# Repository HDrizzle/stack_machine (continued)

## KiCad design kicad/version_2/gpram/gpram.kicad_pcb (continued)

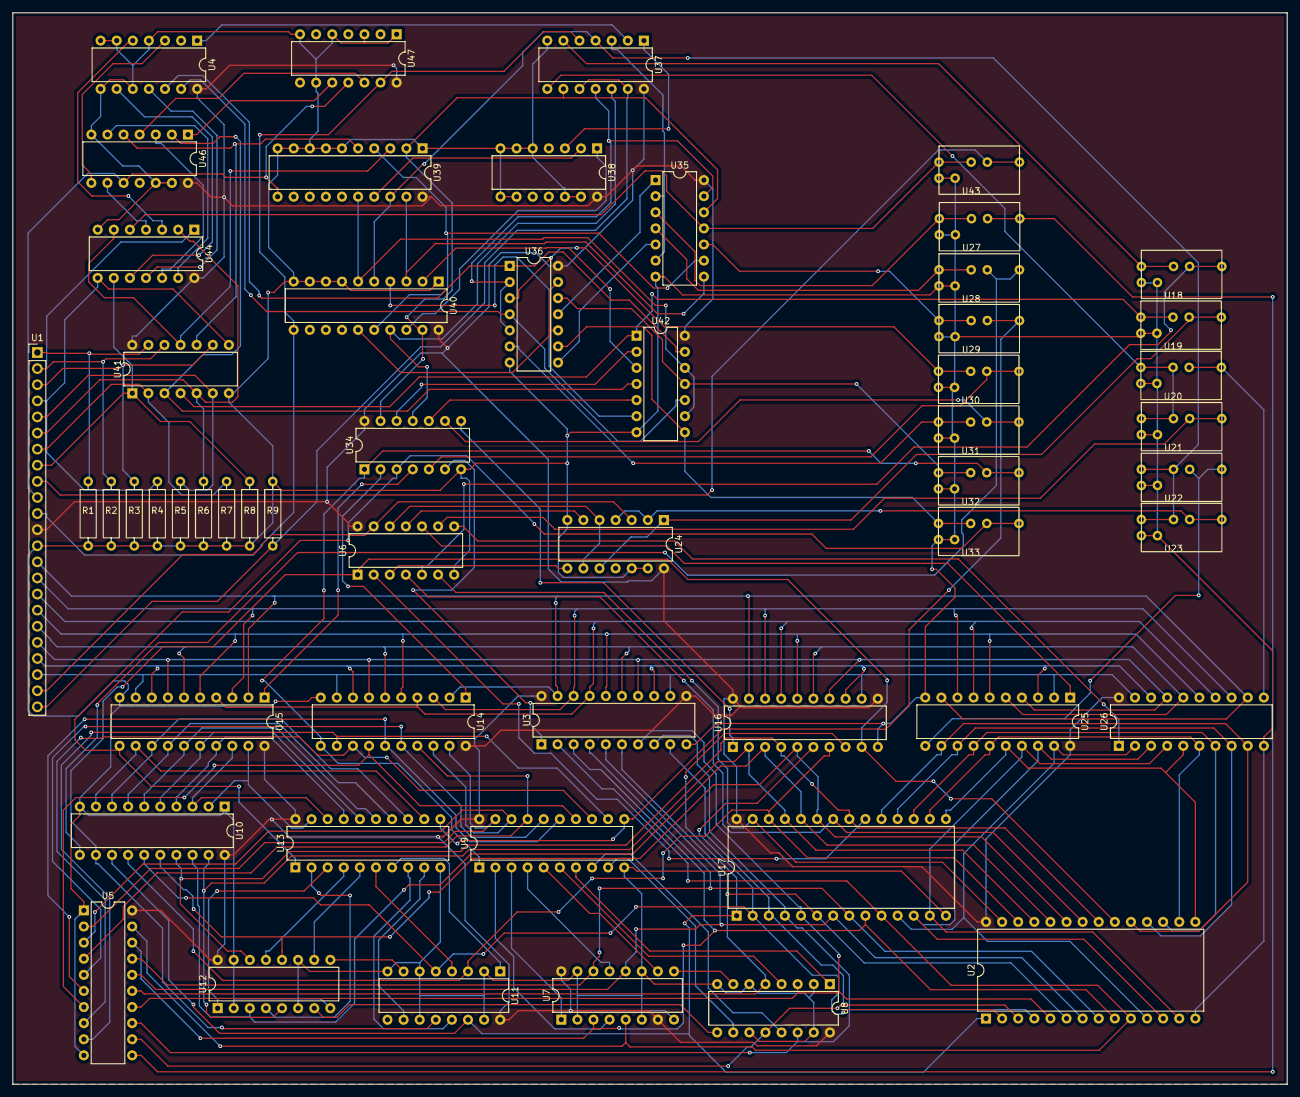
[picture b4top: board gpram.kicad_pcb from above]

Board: 2 copper layers, 201.0 x 169.0 mm, 55 parts (0 on the bottom side), 151 nets.

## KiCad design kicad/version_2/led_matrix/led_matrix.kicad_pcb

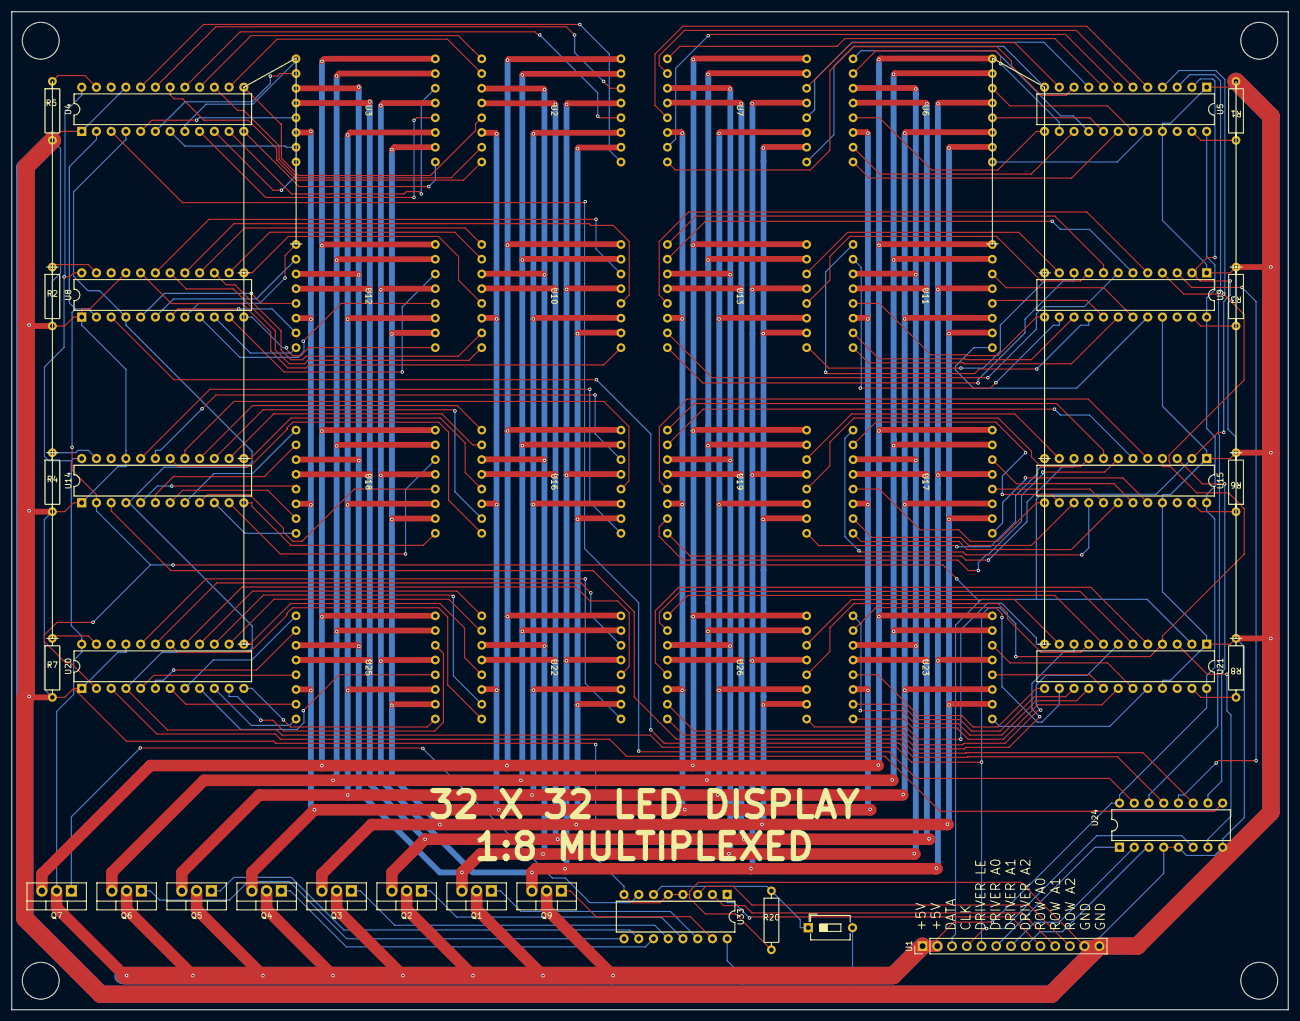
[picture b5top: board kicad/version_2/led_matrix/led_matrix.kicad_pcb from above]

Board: 2 copper layers, 220.0 x 172.0 mm, 45 parts (0 on the bottom side), 172 nets.

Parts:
Q1, Q2, Q3, Q4, Q5, Q6, Q7, Q9: IRF540N; TO-220-3_Vertical
R1, R2, R3, R4, R5, R6, R7, R8, R20: R; 0.4_pitch_resistor
SW1: SW_DIP_x01; SW_DIP_SPSTx01_Slide_6.7x4.1mm_W7.62mm_P2.54mm_LowProfile
U1: PinHeader_1x13_P2.54mm_Vertical
U2, U3, U6, U7, U10, U11, U12, U13, U16, U17, U18, U19, U22, U23, U25, U26: 8_x_8_led_matrix_KWM-30881CVB
U4, U5, U8, U9, U14, U15, U20, U21: DIP-24_W7.62mm
U24, U33: DIP-16_W7.62mm

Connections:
unnamed: Q1.2 (D), Q2.2 (D), Q3.2 (D), Q4.2 (D), Q5.2 (D), Q6.2 (D), Q7.2 (D), Q9.2 (D), SW1.2, U1.1 (V+), U1.2 (V+), U4.24 (V+), U5.24 (V+), U8.24 (V+), U9.24 (V+), U14.24 (V+), U15.24 (V+), U20.24 (V+), U21.24 (V+), U24.16 (V+), U33.16 (V+)
unnamed: Q1.1 (G), U33.14 (Y1)
unnamed: Q1.3 (S), U2.3 (C1), U3.3 (C1), U6.3 (C1), U7.3 (C1), U10.3 (C1), U11.3 (C1), U12.3 (C1), U13.3 (C1), U16.3 (C1), U17.3 (C1), U18.3 (C1), U19.3 (C1), U22.3 (C1), U23.3 (C1), U25.3 (C1), U26.3 (C1)
unnamed: Q2.1 (G), U33.13 (Y2)
unnamed: Q2.3 (S), U2.4 (C2), U3.4 (C2), U6.4 (C2), U7.4 (C2), U10.4 (C2), U11.4 (C2), U12.4 (C2), U13.4 (C2), U16.4 (C2), U17.4 (C2), U18.4 (C2), U19.4 (C2), U22.4 (C2), U23.4 (C2), U25.4 (C2), U26.4 (C2)
unnamed: Q3.1 (G), U33.12 (Y3)
unnamed: Q3.3 (S), U2.10 (C3), U3.10 (C3), U6.10 (C3), U7.10 (C3), U10.10 (C3), U11.10 (C3), U12.10 (C3), U13.10 (C3), U16.10 (C3), U17.10 (C3), U18.10 (C3), U19.10 (C3), U22.10 (C3), U23.10 (C3), U25.10 (C3), U26.10 (C3)
unnamed: Q4.1 (G), U33.11 (Y4)
unnamed: Q4.3 (S), U2.6 (C4), U3.6 (C4), U6.6 (C4), U7.6 (C4), U10.6 (C4), U11.6 (C4), U12.6 (C4), U13.6 (C4), U16.6 (C4), U17.6 (C4), U18.6 (C4), U19.6 (C4), U22.6 (C4), U23.6 (C4), U25.6 (C4), U26.6 (C4)
unnamed: Q5.1 (G), U33.10 (Y5)
unnamed: Q5.3 (S), U2.11 (C5), U3.11 (C5), U6.11 (C5), U7.11 (C5), U10.11 (C5), U11.11 (C5), U12.11 (C5), U13.11 (C5), U16.11 (C5), U17.11 (C5), U18.11 (C5), U19.11 (C5), U22.11 (C5), U23.11 (C5), U25.11 (C5), U26.11 (C5)
unnamed: Q6.1 (G), U33.9 (Y6)
unnamed: Q6.3 (S), U2.15 (C6), U3.15 (C6), U6.15 (C6), U7.15 (C6), U10.15 (C6), U11.15 (C6), U12.15 (C6), U13.15 (C6), U16.15 (C6), U17.15 (C6), U18.15 (C6), U19.15 (C6), U22.15 (C6), U23.15 (C6), U25.15 (C6), U26.15 (C6)
unnamed: Q7.1 (G), U33.7 (Y7)
unnamed: Q7.3 (S), U2.16 (C7), U3.16 (C7), U6.16 (C7), U7.16 (C7), U10.16 (C7), U11.16 (C7), U12.16 (C7), U13.16 (C7), U16.16 (C7), U17.16 (C7), U18.16 (C7), U19.16 (C7), U22.16 (C7), U23.16 (C7), U25.16 (C7), U26.16 (C7)
unnamed: Q9.1 (G), U33.15 (Y0)
unnamed: Q9.3 (S), U2.13 (C0), U3.13 (C0), U6.13 (C0), U7.13 (C0), U10.13 (C0), U11.13 (C0), U12.13 (C0), U13.13 (C0), U16.13 (C0), U17.13 (C0), U18.13 (C0), U19.13 (C0), U22.13 (C0), U23.13 (C0), U25.13 (C0), U26.13 (C0)
unnamed: U1.4 (CLK), U24.6 (E1)
unnamed: U1.3 (Data), U4.2 (D_in), U5.2 (D_in), U8.2 (D_in), U9.2 (D_in), U14.2 (D_in), U15.2 (D_in), U20.2 (D_in), U21.2 (D_in)
unnamed: U1.6 (Driver_A0), U24.1 (A0)
unnamed: U1.7 (Driver_A1), U24.2 (A1)
unnamed: U1.8 (Driver_A2), U24.3 (A2)
unnamed: U1.5 (Driver_LE), U4.4 (LE), U5.4 (LE), U8.4 (LE), U9.4 (LE), U14.4 (LE), U15.4 (LE), U20.4 (LE), U21.4 (LE)
unnamed: U1.9 (Row_A0), U33.1 (A0)
unnamed: U1.10 (Row_A1), U33.2 (A1)
unnamed: U1.11 (Row_A2), U33.3 (A2)
unnamed: U2.9 (R0), U4.20 (O15)
unnamed: U2.14 (R1), U4.19 (O14)
unnamed: U2.8 (R2), U4.18 (O13)
unnamed: U2.12 (R3), U4.17 (O12)
unnamed: U2.1 (R4), U4.16 (O11)
unnamed: U2.7 (R5), U4.15 (O10)
unnamed: U2.2 (R6), U4.14 (O9)
unnamed: U2.5 (R7), U4.13 (O8)
unnamed: U3.9 (R0), U4.12 (O7)
unnamed: U3.14 (R1), U4.11 (O6)
unnamed: U3.8 (R2), U4.10 (O5)
unnamed: U3.12 (R3), U4.9 (O4)
unnamed: U3.1 (R4), U4.8 (O3)
unnamed: U3.7 (R5), U4.7 (O2)
unnamed: U3.2 (R6), U4.6 (O1)
unnamed: U3.5 (R7), U4.5 (O0)
unnamed: R5.1, U4.23 (SET)
unnamed: U5.5 (O0), U7.5 (R7)
unnamed: U5.6 (O1), U7.2 (R6)
unnamed: U5.7 (O2), U7.7 (R5)
unnamed: U5.8 (O3), U7.1 (R4)
unnamed: U5.9 (O4), U7.12 (R3)
unnamed: U5.10 (O5), U7.8 (R2)
unnamed: U5.11 (O6), U7.14 (R1)
unnamed: U5.12 (O7), U7.9 (R0)
unnamed: U5.13 (O8), U6.5 (R7)
unnamed: U5.14 (O9), U6.2 (R6)
unnamed: U5.15 (O10), U6.7 (R5)
unnamed: U5.16 (O11), U6.1 (R4)
unnamed: U5.17 (O12), U6.12 (R3)
unnamed: U5.18 (O13), U6.8 (R2)
unnamed: U5.19 (O14), U6.14 (R1)
unnamed: U5.20 (O15), U6.9 (R0)
unnamed: R1.1, U5.23 (SET)
unnamed: R2.1, U8.23 (SET)
unnamed: R3.1, U9.23 (SET)
unnamed: U8.20 (O15), U10.9 (R0)
unnamed: U8.19 (O14), U10.14 (R1)
unnamed: U8.18 (O13), U10.8 (R2)
unnamed: U8.17 (O12), U10.12 (R3)
unnamed: U8.16 (O11), U10.1 (R4)
unnamed: U8.15 (O10), U10.7 (R5)
unnamed: U8.14 (O9), U10.2 (R6)
unnamed: U8.13 (O8), U10.5 (R7)
unnamed: U9.20 (O15), U11.9 (R0)
unnamed: U9.19 (O14), U11.14 (R1)
unnamed: U9.18 (O13), U11.8 (R2)
unnamed: U9.17 (O12), U11.12 (R3)
unnamed: U9.16 (O11), U11.1 (R4)
unnamed: U9.15 (O10), U11.7 (R5)
unnamed: U9.14 (O9), U11.2 (R6)
unnamed: U9.13 (O8), U11.5 (R7)
unnamed: U8.12 (O7), U12.9 (R0)
unnamed: U8.11 (O6), U12.14 (R1)
unnamed: U8.10 (O5), U12.8 (R2)
unnamed: U8.9 (O4), U12.12 (R3)
unnamed: U8.8 (O3), U12.1 (R4)
unnamed: U8.7 (O2), U12.7 (R5)
unnamed: U8.6 (O1), U12.2 (R6)
unnamed: U8.5 (O0), U12.5 (R7)
unnamed: U9.12 (O7), U13.9 (R0)
unnamed: U9.11 (O6), U13.14 (R1)
unnamed: U9.10 (O5), U13.8 (R2)
unnamed: U9.9 (O4), U13.12 (R3)
unnamed: U9.8 (O3), U13.1 (R4)
unnamed: U9.7 (O2), U13.7 (R5)
unnamed: U9.6 (O1), U13.2 (R6)
unnamed: U9.5 (O0), U13.5 (R7)
unnamed: U14.3 (CLK), U24.11 (Y4)
unnamed: R1.2, R2.2, R3.2, R4.2, R5.2, R6.2, R7.2, R8.2, R20.2, U1.12 (GND), U1.13 (GND), U4.1 (GND), U4.21 (OE#), U5.1 (GND), U5.21 (OE#), U8.1 (GND), U8.21 (OE#), U9.1 (GND), U9.21 (OE#), U14.1 (GND), U14.21 (OE#), U15.1 (GND), U15.21 (OE#), U20.1 (GND), U20.21 (OE#), U21.1 (GND), U21.21 (OE#), U24.4 (E2#), U24.5 (E3#), U24.8 (GND), U33.4 (E2#), U33.5 (E3#), U33.8 (GND)
unnamed: U14.5 (O0), U18.5 (R7)
unnamed: U14.6 (O1), U18.2 (R6)
unnamed: U14.7 (O2), U18.7 (R5)
unnamed: U14.8 (O3), U18.1 (R4)
unnamed: U14.9 (O4), U18.12 (R3)
unnamed: U14.10 (O5), U18.8 (R2)
unnamed: U14.11 (O6), U18.14 (R1)
unnamed: U14.12 (O7), U18.9 (R0)
unnamed: U14.13 (O8), U16.5 (R7)
unnamed: U14.14 (O9), U16.2 (R6)
unnamed: U14.15 (O10), U16.7 (R5)
unnamed: U14.16 (O11), U16.1 (R4)
unnamed: U14.17 (O12), U16.12 (R3)
unnamed: U14.18 (O13), U16.8 (R2)
unnamed: U14.19 (O14), U16.14 (R1)
unnamed: U14.20 (O15), U16.9 (R0)
unnamed: R4.1, U14.23 (SET)
unnamed: U15.3 (CLK), U24.10 (Y5)
unnamed: U15.5 (O0), U19.5 (R7)
unnamed: U15.6 (O1), U19.2 (R6)
unnamed: U15.7 (O2), U19.7 (R5)
unnamed: U15.8 (O3), U19.1 (R4)
unnamed: U15.9 (O4), U19.12 (R3)
unnamed: U15.10 (O5), U19.8 (R2)
unnamed: U15.11 (O6), U19.14 (R1)
unnamed: U15.12 (O7), U19.9 (R0)
unnamed: U15.13 (O8), U17.5 (R7)
unnamed: U15.14 (O9), U17.2 (R6)
unnamed: U15.15 (O10), U17.7 (R5)
unnamed: U15.16 (O11), U17.1 (R4)
unnamed: U15.17 (O12), U17.12 (R3)
unnamed: U15.18 (O13), U17.8 (R2)
unnamed: U15.19 (O14), U17.14 (R1)
unnamed: U15.20 (O15), U17.9 (R0)
unnamed: R6.1, U15.23 (SET)
unnamed: U20.3 (CLK), U24.9 (Y6)
unnamed: U20.5 (O0), U25.5 (R7)
unnamed: U20.6 (O1), U25.2 (R6)
unnamed: U20.7 (O2), U25.7 (R5)
unnamed: U20.8 (O3), U25.1 (R4)
unnamed: U20.9 (O4), U25.12 (R3)
unnamed: U20.10 (O5), U25.8 (R2)
unnamed: U20.11 (O6), U25.14 (R1)
unnamed: U20.12 (O7), U25.9 (R0)
unnamed: U20.13 (O8), U22.5 (R7)
unnamed: U20.14 (O9), U22.2 (R6)
unnamed: U20.15 (O10), U22.7 (R5)
unnamed: U20.16 (O11), U22.1 (R4)
unnamed: U20.17 (O12), U22.12 (R3)
unnamed: U20.18 (O13), U22.8 (R2)
unnamed: U20.19 (O14), U22.14 (R1)
unnamed: U20.20 (O15), U22.9 (R0)
unnamed: R7.1, U20.23 (SET)
unnamed: U21.3 (CLK), U24.7 (Y7)
unnamed: U21.5 (O0), U26.5 (R7)
unnamed: U21.6 (O1), U26.2 (R6)
unnamed: U21.7 (O2), U26.7 (R5)
unnamed: U21.8 (O3), U26.1 (R4)
unnamed: U21.9 (O4), U26.12 (R3)
unnamed: U21.10 (O5), U26.8 (R2)
unnamed: U21.11 (O6), U26.14 (R1)
unnamed: U21.12 (O7), U26.9 (R0)
unnamed: U21.13 (O8), U23.5 (R7)
unnamed: U21.14 (O9), U23.2 (R6)
unnamed: U21.15 (O10), U23.7 (R5)
unnamed: U21.16 (O11), U23.1 (R4)
unnamed: U21.17 (O12), U23.12 (R3)
unnamed: U21.18 (O13), U23.8 (R2)
unnamed: U21.19 (O14), U23.14 (R1)
unnamed: U21.20 (O15), U23.9 (R0)
unnamed: R8.1, U21.23 (SET)
unnamed: U4.3 (CLK), U24.15 (Y0)
unnamed: U5.3 (CLK), U24.14 (Y1)
unnamed: U8.3 (CLK), U24.13 (Y2)
unnamed: U9.3 (CLK), U24.12 (Y3)
unnamed: R20.1, SW1.1, U33.6 (E1)

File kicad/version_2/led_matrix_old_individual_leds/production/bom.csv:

Designator,Footprint,Quantity,Value,LCSC Part #
"Q1, Q2, Q3, Q4, Q5, Q6, Q7, Q9",TO-220-3_Vertical,8,IRF540N,
"R10, R11, R12, R13, R20, R5, R6, R8, R9",0.4_pitch_resistor,9,R,
SW1,SW_DIP_SPSTx01_Slide_6.7x4.1mm_W7.62mm_P2.54mm_LowProfile,1,SW_DIP_x01,
U1,PinHeader_1x13_P2.54mm_Vertical,1,~,
"U10, U12, U13, U18, U19, U4, U6, U8",DIP-24_W7.62mm,8,~,
"U11, U5, U7, U9",led_block_16_x_8_left,4,~,
"U20, U21, U22, U23",led_block_16_x_8_right,4,~,
"U24, U33",DIP-16_W7.62mm,2,~,

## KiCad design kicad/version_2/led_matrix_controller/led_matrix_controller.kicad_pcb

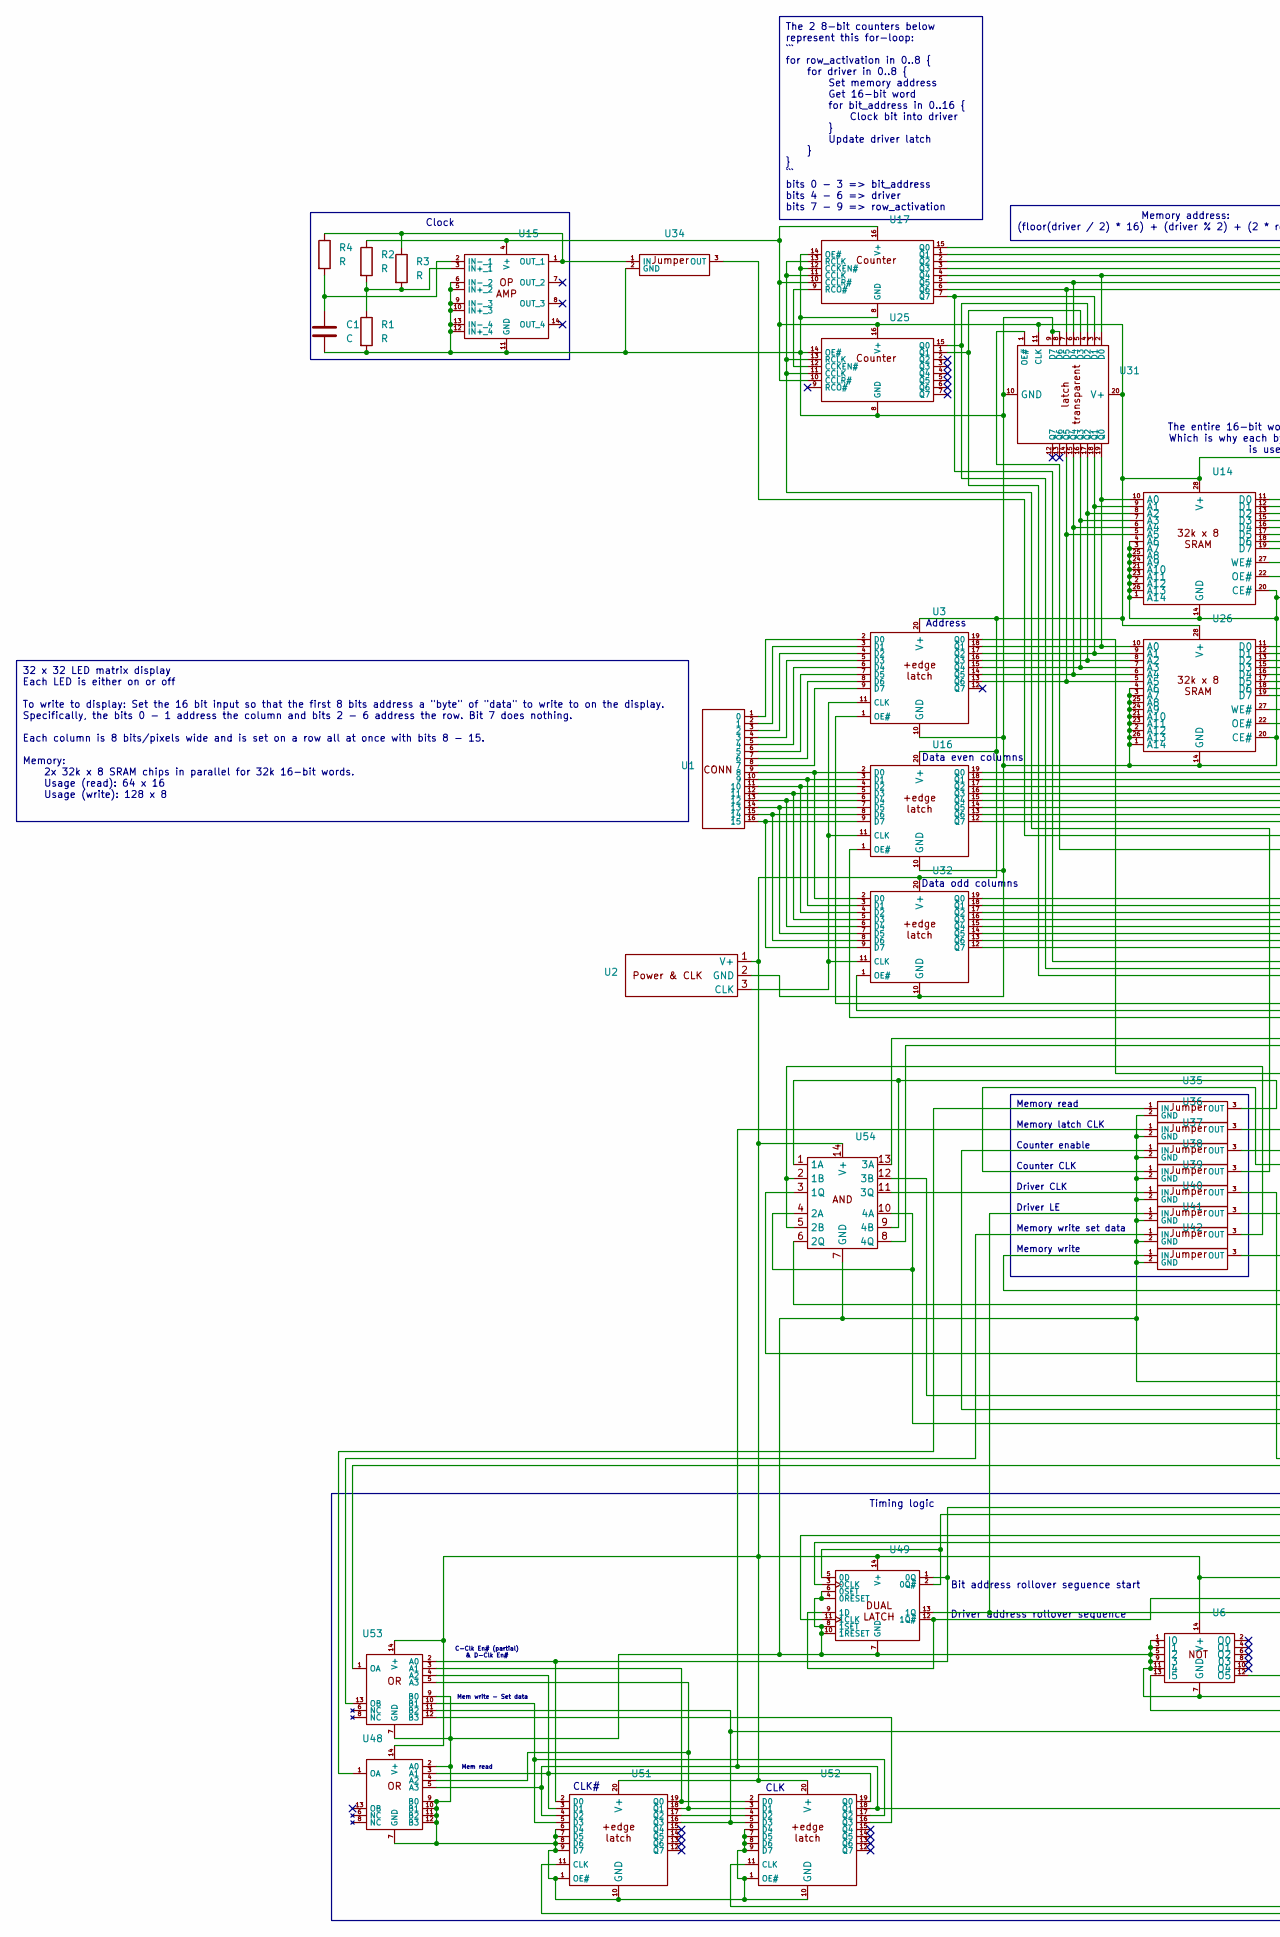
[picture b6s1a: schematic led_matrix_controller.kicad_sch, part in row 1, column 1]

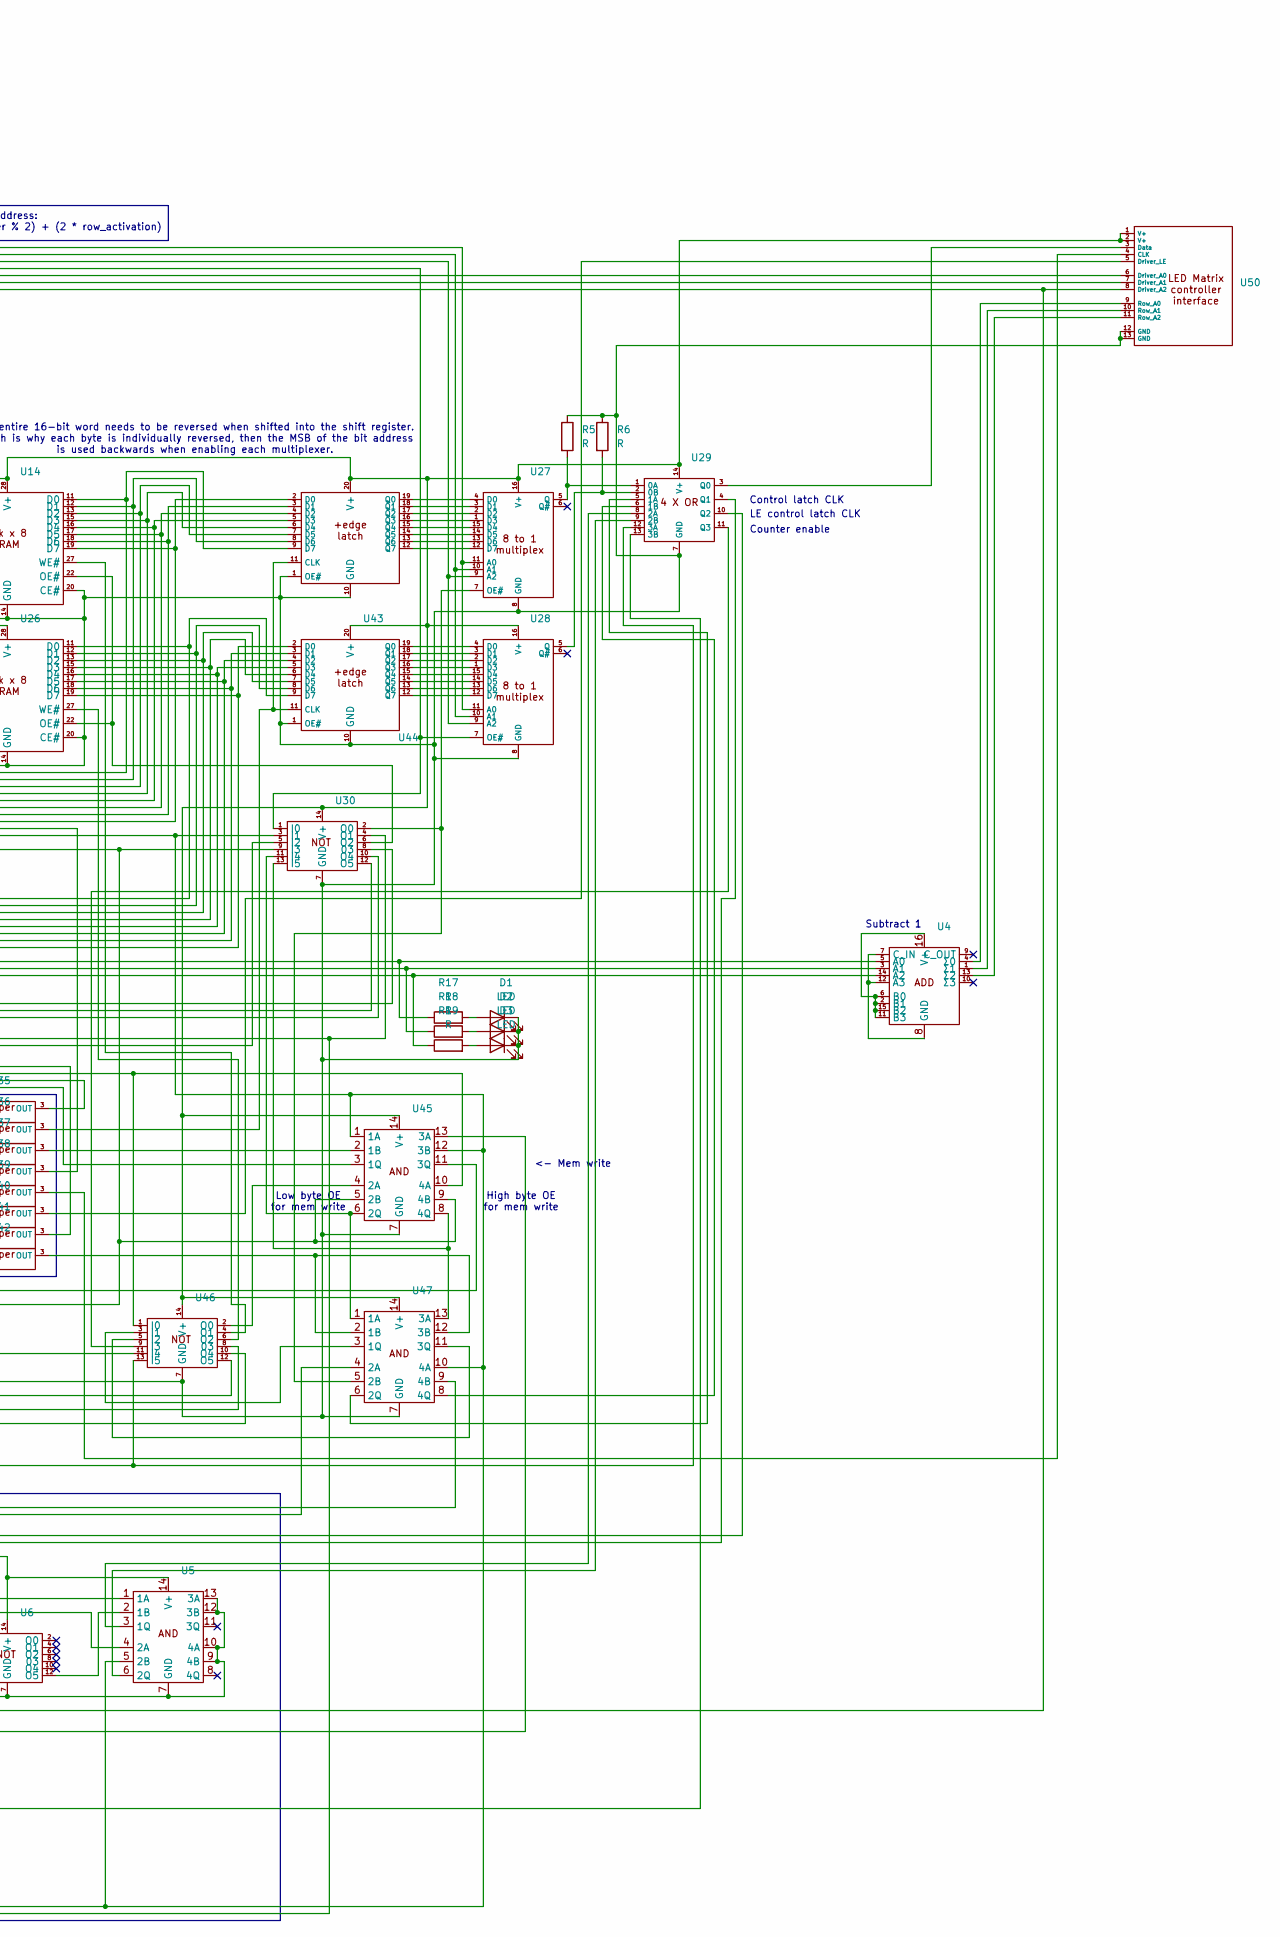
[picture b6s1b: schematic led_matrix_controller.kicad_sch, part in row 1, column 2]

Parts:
C1: C; CP_Radial_D4.0mm_P2.00mm
D1, D2, D3: LED; LED_D3.0mm
R1, R2, R3, R4, R5, R6, R17, R18, R19: R; 0.4_pitch_resistor
U1: PinHeader_1x16_P2.54mm_Vertical
U2: PinHeader_1x03_P2.54mm_Vertical
U3, U16, U31, U32, U43, U44, U51, U52: DIP-20_W7.62mm
U4, U17, U25, U27, U28: DIP-16_W7.62mm
U5, U6, U15, U29, U30, U45, U46, U47, U48, U49, U53, U54: DIP-14_W7.62mm
U14, U26: DIP-28_W15.24mm
U34, U35, U36, U37, U38, U39, U40, U41, U42: jumper
U50: PinHeader_1x13_P2.54mm_Vertical

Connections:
unnamed: D1.2 (A), R17.2
unnamed: C1.2, D1.1 (K), D2.1 (K), D3.1 (K), R1.2, R5.1, R6.1, U2.2 (GND), U3.10 (GND), U5.7 (GND), U5.9 (4B), U5.10 (4A), U5.12 (3B), U5.13 (3A), U6.1 (I0), U6.3 (I1), U6.5 (I2), U6.7 (GND), U6.9 (I3), U6.11 (I4), U14.1 (A14), U14.2 (A12), U14.3 (A7), U14.4 (A6), U14.14 (GND), U14.20 (CE#), U14.21 (A10), U14.23 (A11), U14.24 (A9), U14.25 (A8), U14.26 (A13), U15.5 (IN+_2), U15.6 (IN-_2), U15.9 (IN-_3), U15.10 (IN+_3), U15.11 (GND), U15.12 (IN+_4), U15.13 (IN-_4), U16.10 (GND), U17.8 (GND), U17.12 (CCKEN#), U17.14 (OE#), U25.8 (GND), U25.14 (OE#), U26.1 (A14), U26.2 (A12), U26.3 (A7), U26.4 (A6), U26.14 (GND), U26.20 (CE#), U26.21 (A10), U26.23 (A11), U26.24 (A9), U26.25 (A8), U26.26 (A13), U27.8 (GND), U28.8 (GND), U29.7 (GND), U30.7 (GND), U31.8 (D6), U31.9 (D7), U31.10 (GND), U32.10 (GND), U34.2 (GND), U35.2 (GND), U36.2 (GND), U37.2 (GND), U38.2 (GND), U39.2 (GND), U40.2 (GND), U41.2 (GND), U42.2 (GND), U43.1 (OE#), U43.10 (GND), U44.1 (OE#), U44.10 (GND), U45.7 (GND), U46.7 (GND), U47.7 (GND), U48.2 (A0), U48.7 (GND), U48.9 (B0), U48.10 (B1), U48.11 (B2), U48.12 (B3), U49.4 (0RESET), U49.6 (0SET), U49.7 (GND), U49.8 (1SET), U49.10 (1RESET), U50.12 (GND), U50.13 (GND), U51.1 (OE#), U51.6 (D4), U51.7 (D5), U51.8 (D6), U51.9 (D7), U51.10 (GND), U52.1 (OE#), U52.6 (D4), U52.7 (D5), U52.8 (D6), U52.9 (D7), U52.10 (GND), U53.7 (GND), U53.9 (B0), U54.7 (GND)
unnamed: D2.2 (A), R18.2
unnamed: D3.2 (A), R19.2
unnamed: U1.1 (0), U3.2 (D0)
unnamed: U1.2 (1), U3.3 (D1)
unnamed: U1.3 (2), U3.4 (D2)
unnamed: U1.4 (3), U3.5 (D3)
unnamed: U1.5 (4), U3.6 (D4)
unnamed: U1.6 (5), U3.7 (D5)
unnamed: U1.7 (6), U3.8 (D6)
unnamed: U1.8 (7), U3.9 (D7)
unnamed: U1.9 (8), U16.2 (D0), U32.2 (D0)
unnamed: U1.10 (9), U16.3 (D1), U32.3 (D1)
unnamed: U1.11 (10), U16.4 (D2), U32.4 (D2)
unnamed: U1.12 (11), U16.5 (D3), U32.5 (D3)
unnamed: U1.13 (12), U16.6 (D4), U32.6 (D4)
unnamed: U1.14 (13), U16.7 (D5), U32.7 (D5)
unnamed: U1.15 (14), U16.8 (D6), U32.8 (D6)
unnamed: U1.16 (15), U16.9 (D7), U32.9 (D7)
unnamed: U3.1 (OE#), U30.8 (03)
unnamed: U3.19 (Q0), U45.10 (4A), U46.1 (I0)
unnamed: U4.7 (C_IN), U4.8 (GND), U4.12 (A3)
unnamed: U4.2 (B1), U4.6 (B0), U4.11 (B3), U4.15 (B2), U4.16 (V+)
unnamed: U4.4 (Σ0), U50.9 (Row_A0)
unnamed: U4.1 (Σ1), U50.10 (Row_A1)
unnamed: U4.13 (Σ2), U50.11 (Row_A2)
unnamed: U5.2 (1B), U6.12 (O5)
unnamed: U3.18 (Q1), U14.10 (A0), U26.10 (A0), U31.19 (Q0)
unnamed: U3.17 (Q2), U14.9 (A1), U26.9 (A1), U31.18 (Q1)
unnamed: U3.16 (Q3), U14.8 (A2), U26.8 (A2), U31.17 (Q2)
unnamed: U3.15 (Q4), U14.7 (A3), U26.7 (A3), U31.16 (Q3)
unnamed: U3.14 (Q5), U14.6 (A4), U26.6 (A4), U31.15 (Q4)
unnamed: U3.13 (Q6), U14.5 (A5), U26.5 (A5), U31.14 (Q5)
unnamed: U14.11 (D0), U16.19 (Q0), U44.9 (D7)
unnamed: U14.12 (D1), U16.18 (Q1), U44.8 (D6)
unnamed: U14.13 (D2), U16.17 (Q2), U44.7 (D5)
unnamed: U14.15 (D3), U16.16 (Q3), U44.6 (D4)
unnamed: U14.16 (D4), U16.15 (Q4), U44.5 (D3)
unnamed: U14.17 (D5), U16.14 (Q5), U44.4 (D2)
unnamed: U14.18 (D6), U16.13 (Q6), U44.3 (D1)
unnamed: U14.19 (D7), U16.12 (Q7), U44.2 (D0)
unnamed: U14.22 (OE#), U26.22 (OE#), U30.6 (O2)
unnamed: R2.1, U2.1 (V+), U3.20 (V+), U5.14 (V+), U6.14 (V+), U14.28 (V+), U15.4 (V+), U16.20 (V+), U17.10 (CCLR#), U17.16 (V+), U25.10 (CCLR#), U25.16 (V+), U26.28 (V+), U27.16 (V+), U28.16 (V+), U29.14 (V+), U30.14 (V+), U31.11 (CLK), U31.20 (V+), U32.20 (V+), U43.20 (V+), U44.20 (V+), U45.14 (V+), U46.14 (V+), U47.14 (V+), U48.14 (V+), U49.14 (V+), U50.1 (V+), U50.2 (V+), U51.20 (V+), U52.20 (V+), U53.14 (V+), U54.14 (V+)
unnamed: U14.27 (WE#), U46.4 (O1)
unnamed: R1.1, R2.2, R3.2, U15.3 (IN+_1)
unnamed: C1.1, R4.2, U15.2 (IN-_1)
unnamed: R3.1, R4.1, U15.1 (OUT_1), U34.1 (IN)
unnamed: U2.3 (CLK), U3.11 (CLK), U16.11 (CLK), U32.11 (CLK)
unnamed: U16.1 (OE#), U30.10 (O4)
unnamed: U17.11 (CCLK), U17.13 (RCLK), U25.11 (CCLK), U25.13 (RCLK), U38.3 (OUT)
unnamed: U17.15 (Q0), U27.11 (A0), U28.11 (A0)
unnamed: U17.1 (Q1), U27.10 (A1), U28.10 (A1)
unnamed: U17.2 (Q2), U27.9 (A2), U28.9 (A2)
unnamed: U17.3 (Q3), U28.7 (OE#), U30.1 (I0)
unnamed: U17.4 (Q4), U31.2 (D0), U50.6 (Driver_A0)
unnamed: U17.5 (Q5), U31.6 (D4), U50.7 (Driver_A1)
unnamed: U6.13 (I5), U17.6 (Q6), U31.7 (D5), U50.8 (Driver_A2)
unnamed: R17.1, U4.5 (A0), U17.7 (Q7), U31.3 (D1)
unnamed: U17.9 (RCO#), U25.12 (CCKEN#)
unnamed: R18.1, U4.3 (A1), U25.15 (Q0), U31.4 (D2)
unnamed: R19.1, U4.14 (A2), U25.1 (Q1), U31.5 (D3)
unnamed: U26.11 (D0), U32.19 (Q0), U43.9 (D7)
unnamed: U26.12 (D1), U32.18 (Q1), U43.8 (D6)
unnamed: U26.13 (D2), U32.17 (Q2), U43.7 (D5)
unnamed: U26.15 (D3), U32.16 (Q3), U43.6 (D4)
unnamed: U26.16 (D4), U32.15 (Q4), U43.5 (D3)
unnamed: U26.17 (D5), U32.14 (Q5), U43.4 (D2)
unnamed: U26.18 (D6), U32.13 (Q6), U43.3 (D1)
unnamed: U26.19 (D7), U32.12 (Q7), U43.2 (D0)
unnamed: U26.27 (WE#), U46.6 (O2)
unnamed: U27.4 (D0), U44.19 (Q0)
unnamed: U27.3 (D1), U44.18 (Q1)
unnamed: U27.2 (D2), U44.17 (Q2)
unnamed: U27.1 (D3), U44.16 (Q3)
unnamed: U27.15 (D4), U44.15 (Q4)
unnamed: U27.14 (D5), U44.14 (Q5)
unnamed: U27.13 (D6), U44.13 (Q6)
unnamed: U27.12 (D7), U44.12 (Q7)
unnamed: U27.7 (OE#), U30.2 (O0), U47.5 (2B)
unnamed: R5.2, U27.5 (Q), U29.1 (0A)
unnamed: U28.4 (D0), U43.19 (Q0)
unnamed: U28.3 (D1), U43.18 (Q1)
unnamed: U28.2 (D2), U43.17 (Q2)
unnamed: U28.1 (D3), U43.16 (Q3)
unnamed: U28.15 (D4), U43.15 (Q4)
unnamed: U28.14 (D5), U43.14 (Q5)
unnamed: U28.13 (D6), U43.13 (Q6)
unnamed: U28.12 (D7), U43.12 (Q7)
unnamed: R6.2, U28.5 (Q), U29.2 (0B)
unnamed: U29.5 (1A), U47.6 (2Q)
unnamed: U29.6 (1B), U47.8 (4Q)
unnamed: U5.3 (1Q), U29.8 (2A)
unnamed: U5.6 (2Q), U29.9 (2B)
unnamed: U29.12 (3A), U46.13 (I5), U53.1 (OA)
unnamed: U29.13 (3B), U36.1 (IN), U48.5 (A3), U51.4 (D2), U52.18 (Q1)
unnamed: U29.3 (Q0), U50.3 (Data)
unnamed: U29.4 (Q1), U49.3 (0CLK)
unnamed: U29.10 (Q2), U49.11 (1CLK)
unnamed: U29.11 (Q3), U46.9 (I3)
unnamed: U5.5 (2B), U30.3 (I1), U34.3 (OUT), U45.1 (1A), U45.12 (3B), U47.10 (4A), U52.11 (CLK)
unnamed: U30.5 (I2), U54.8 (4Q)
unnamed: U30.9 (I3), U31.1 (OE#), U45.5 (2B), U45.9 (4B), U54.6 (2Q)
unnamed: U30.11 (I4), U45.6 (2Q), U47.1 (1A)
unnamed: U30.13 (I5), U45.8 (4Q), U47.13 (3A)
unnamed: U30.4 (O1), U51.11 (CLK), U54.13 (3A)
unnamed: U30.12 (O5), U32.1 (OE#)
unnamed: U35.1 (IN), U48.1 (OA)
unnamed: U35.3 (OUT), U54.1 (1A), U54.9 (4B)
unnamed: U36.3 (OUT), U43.11 (CLK), U44.11 (CLK)
unnamed: U37.1 (IN), U46.8 (03)
unnamed: U37.3 (OUT), U45.2 (1B)
unnamed: U38.1 (IN), U45.3 (1Q)
unnamed: U39.1 (IN), U54.11 (3Q)
unnamed: U39.3 (OUT), U50.4 (CLK)
unnamed: U5.4 (2A), U40.1 (IN), U49.13 (1Q)
unnamed: U40.3 (OUT), U50.5 (Driver_LE)
unnamed: U41.1 (IN), U53.13 (OB)
unnamed: U41.3 (OUT), U54.2 (1B), U54.5 (2B)
unnamed: U42.1 (IN), U45.11 (3Q)
unnamed: U42.3 (OUT), U47.2 (1B), U47.12 (3B)
unnamed: U45.4 (2A), U46.2 (O0)
unnamed: U45.13 (3A), U51.16 (Q3), U52.5 (D3), U53.11 (B2)
unnamed: U46.3 (I1), U47.3 (1Q)
unnamed: U46.5 (I2), U47.11 (3Q)
unnamed: U46.11 (I4), U54.3 (1Q)
unnamed: U46.10 (O4), U54.4 (2A), U54.10 (4A)
unnamed: U46.12 (O5), U54.12 (3B)
unnamed: U47.4 (2A), U49.2 (0Q#), U49.5 (0D)
unnamed: U47.9 (4B), U49.1 (0Q), U51.2 (D0), U53.2 (A0)
unnamed: U48.3 (A1), U51.3 (D1), U52.19 (Q0), U53.4 (A2)
unnamed: U48.4 (A2), U51.18 (Q1), U52.3 (D1), U53.5 (A3)
unnamed: U5.1 (1A), U49.9 (1D), U49.12 (1Q#)
unnamed: U51.5 (D3), U52.17 (Q2), U53.10 (B1)
unnamed: U51.19 (Q0), U52.2 (D0), U53.3 (A1)
unnamed: U51.17 (Q2), U52.4 (D2)
unnamed: U52.16 (Q3), U53.12 (B3)

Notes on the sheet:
Memory address: (floor(driver / 2) * 16) + (driver % 2) + (2 * row_activation)
The 2 8-bit counters below represent this for-loop: ``` for row_activation in 0..8 { for driver in 0..8 { Set memory address Get 16-bit word for bit_address in 0..16 { Clock bit into driver } Update driver latch } } ``` bits 0 - 3 => bit_address bits 4 - 6 => driver bits 7 - 9 => row_activation
32 x 32 LED matrix display Each LED is either on or off To write to display: Set the 16 bit input so that the first 8 bits address a "byte" of "data" to write to on the display. Specifically, the bits 0 - 1 address the column and bits 2 - 6 address the row. Bit 7 does nothing. Each column is 8 bits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
Memory read Memory latch CLK Counter enable Counter CLK Driver CLK Driver LE Memory write set data Memory write
Timing logic
Clock
Control latch CLK
Data even columns
Low byte OE for mem write
Address
<- Mem write
CLK
The entire 16-bit word needs to be reversed when shifted into the shift register. Which is why each byte is individually reversed, then the MSB of the bit address is used backwards when enabling each multiplexer.
Mem write - Set data
High byte OE for mem write
Mem read
C-Clk En# (partial) & D-Clk En#
Driver address rollover sequence
Data odd columns
Bit address rollover seguence start
Counter enable
LE control latch CLK
Subtract 1
CLK#

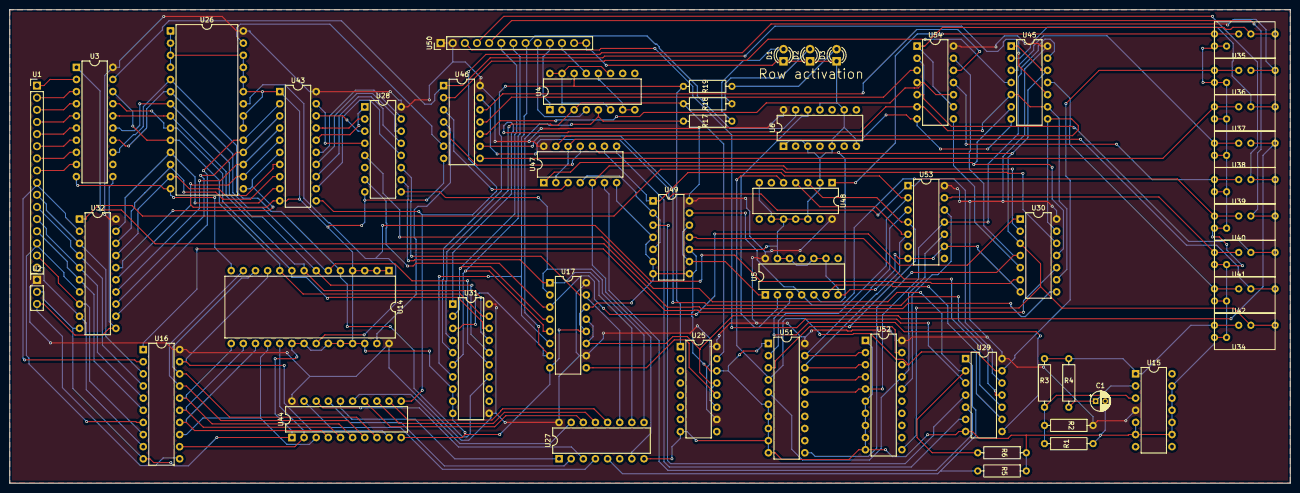
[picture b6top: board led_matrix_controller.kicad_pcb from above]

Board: 2 copper layers, 268.0 x 99.1 mm, 52 parts (0 on the bottom side), 137 nets.

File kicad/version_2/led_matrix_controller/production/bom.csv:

Designator,Footprint,Quantity,Value,LCSC Part #
C1,CP_Radial_D4.0mm_P2.00mm,1,C,
"D1, D2, D3",LED_D3.0mm,3,LED,
"R1, R17, R18, R19, R2, R3, R4",0.4_pitch_resistor,7,R,
U1,PinHeader_1x16_P2.54mm_Vertical,1,~,
"U14, U26",DIP-28_W15.24mm,2,~,
"U15, U29, U30, U45, U46, U47, U48, U49, U53, U54",DIP-14_W7.62mm,10,~,
"U16, U3, U31, U32, U43, U44, U51, U52",DIP-20_W7.62mm,8,~,
"U17, U25, U27, U28",DIP-16_W7.62mm,4,~,
U2,PinHeader_1x03_P2.54mm_Vertical,1,~,
"U34, U35, U36, U37, U38, U39, U40, U41, U42",jumper,9,~,
U50,PinHeader_1x13_P2.54mm_Vertical,1,~,
